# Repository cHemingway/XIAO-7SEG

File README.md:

## Xiao 7 Seg
7 Seg display shield for SeeedStudio Xiao / Adafruit QtPy

Uses Guangcai Display's tiny SMT displays, in white but you can get other colors, see [LCSC](https://www.lcsc.com/product-detail/C22462653.html)

Mainly as a trial of JLCPCB assembly workflow

### Todo
- Order and bringup
- Make a circuitpython library or something

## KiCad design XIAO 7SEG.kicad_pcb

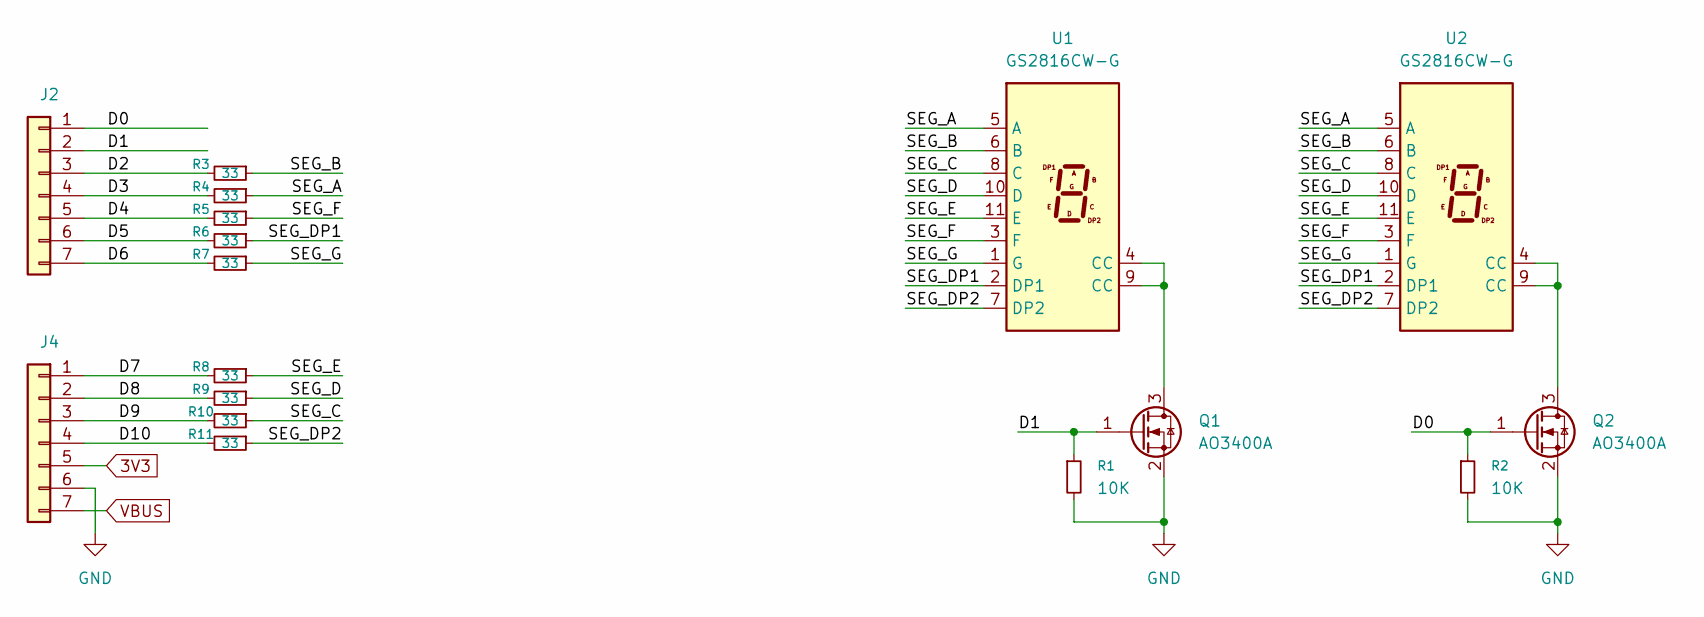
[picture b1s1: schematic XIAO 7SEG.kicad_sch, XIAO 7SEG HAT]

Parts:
J2, J4: Conn_01x07; Xiao-Hat-Pins
Q1, Q2: AO3400A; SOT-23; LCSC PN C20917
R1, R2: 10K; R_0402_1005Metric; LCSC PN C25744
R3, R4, R5, R6, R7, R8, R9, R10, R11: 33; R_0402_1005Metric; LCSC PN C25105
U1, U2: GS2816CW-G; GS2816ACX-X_Short; LCSC PN C22462653

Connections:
3V3: J4.5
/D0: J2.1, Q2.1 (G), R2.1
/D1: J2.2, Q1.1 (G), R1.1
/D2: J2.3, R3.2
/D3: J2.4, R4.2
/D4: J2.5, R5.2
/D5: J2.6, R6.2
/D6: J2.7, R7.2
/D7: J4.1, R8.2
/D8: J4.2, R9.2
/D9: J4.3, R10.2
/D10: J4.4, R11.2
/SEG_A: R4.1, U1.5 (A), U2.5 (A)
/SEG_B: R3.1, U1.6 (B), U2.6 (B)
/SEG_C: R10.1, U1.8 (C), U2.8 (C)
/SEG_D: R9.1, U1.10 (D), U2.10 (D)
/SEG_DP1: R6.1, U1.2 (DP1), U2.2 (DP1)
/SEG_DP2: R11.1, U1.7 (DP2), U2.7 (DP2)
/SEG_E: R8.1, U1.11 (E), U2.11 (E)
/SEG_F: R5.1, U1.3 (F), U2.3 (F)
/SEG_G: R7.1, U1.1 (G), U2.1 (G)
GND: J4.6, Q1.2 (S), Q2.2 (S), R1.2, R2.2
unnamed: Q1.3 (D), U1.4 (CC), U1.9 (CC)
unnamed: Q2.3 (D), U2.4 (CC), U2.9 (CC)
VBUS: J4.7

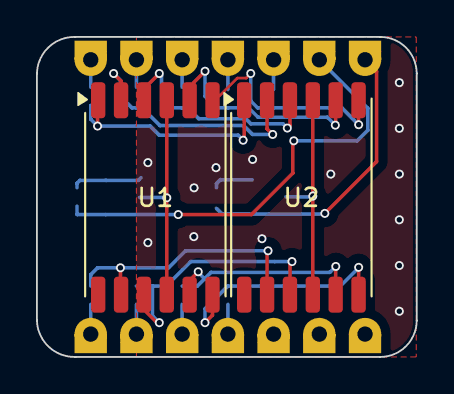
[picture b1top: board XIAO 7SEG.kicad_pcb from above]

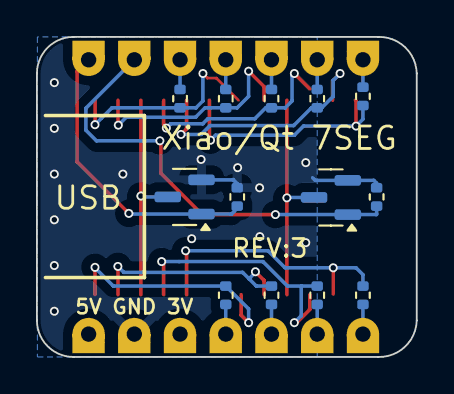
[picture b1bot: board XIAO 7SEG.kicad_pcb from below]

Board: 2 copper layers, 21.1 x 17.8 mm, 17 parts (13 on the bottom side), 23 nets.

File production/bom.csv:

Designator,Footprint,Quantity,Value,LCSC Part #
"Q1, Q2",SOT-23,2,AO3400A,C20917
"R1, R2",0402,2,10K,C25744
"U1, U2",GS2816ACX-X_Short,2,GS2816CW-G,C22462653

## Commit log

2025-08-24 Initial Commit, ready for manufacture
2025-08-24 Add PDF schematic
2025-08-25 Increase min track/gap to 0.154mm
2025-08-28 V2: Add series resistors
2025-08-29 Renumber pins to make easier
2025-08-30 Add supply voltages to silk
